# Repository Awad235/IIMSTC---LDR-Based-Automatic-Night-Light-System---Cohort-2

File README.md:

# 🌙 LDR Based Automatic Night Light System

---

## 📋 Overview

The **LDR Based Automatic Night Light System** is a simple, energy-efficient automatic lighting controller. It uses a Light Dependent Resistor (LDR) to detect ambient light levels and automatically turns an LED ON during darkness and OFF during daylight.

This project demonstrates:
- Light sensing using LDR
- Transistor-based switching
- PCB design using KiCad
- Sustainable energy usage (aligns with SDG 7: Affordable and Clean Energy)

**Designed & simulated in KiCad**  
**Power Supply:** 5V DC

---

## ✨ Features

- Fully automatic operation (no manual switch needed)
- Low power consumption
- Cost-effective and easy to build
- Compact PCB design
- Real-world applications: street lights, garden lights, corridor lighting, security systems

---

## 🛠️ Components Used

| Sl. No | Component                  | Specification                  |
|--------|----------------------------|--------------------------------|
| 1      | Light Dependent Resistor   | LDR03 Photoresistor            |
| 2      | Transistor                 | BC817-40 (NPN)                 |
| 3      | LED                        | SML-LX1206SUGC-TR (Green)      |
| 4      | Resistor R1                | 82 kΩ                          |
| 5      | Resistor R2                | 82 kΩ                          |
| 6      | DC Power Connector         | 2-Pin connector (J1)           |
| 7      | Power Supply               | 5V DC                          |

**Note:** The schematic file (source of truth) shows R2 = 82 kΩ.

---

## 📐 Circuit Schematic

**Key Connections:**
- LDR (R3) + R1 form voltage divider for transistor base
- Q1 (BC817-40) acts as electronic switch
- R2 limits current through the LED

---

## 🖨️ PCB Layout

---

## 📦 3D View

)

---

## 🔬 How It Works

The system works on the principle of variation in resistance of the LDR with respect to light intensity.

- **Daytime (bright light):** LDR resistance drops sharply → voltage at transistor base becomes too low → transistor stays OFF → LED remains OFF.
- **Nighttime (low light):** LDR resistance increases significantly → sufficient base voltage turns the transistor ON → current flows through R2 and LED → LED glows automatically.

The transistor (BC817-40) acts as a simple electronic switch, and the whole circuit runs on 5V DC with zero standby power when the LED is off.

---

## 🚀 How to Build & Test

1. Use the provided KiCad schematic & layout (or recreate from images)
2. Fabricate the PCB
3. Solder components exactly as shown in the 3D view
4. Connect 5V DC supply to J1
5. Cover the LDR with your hand → LED should turn ON
6. Shine light on the LDR → LED should turn OFF

**Pro tip:** Test everything on a breadboard first before soldering!

---

## 🛡️ License

Open-source under the **MIT License**. Feel free to use, modify, and share!

---

**Made with ❤️ in Bengaluru**  
**Last updated:** March 2026

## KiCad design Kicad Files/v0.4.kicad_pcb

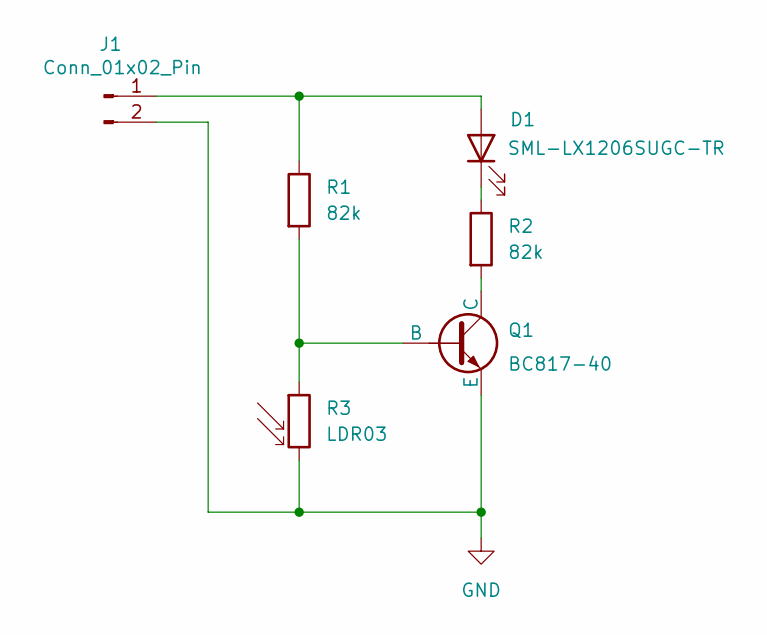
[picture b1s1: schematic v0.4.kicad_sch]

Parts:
D1: SML-LX1206SUGC-TR; LED_1206_3216Metric
J1: Conn_01x02_Pin; PinHeader_1x02_P2.54mm_Vertical
Q1: BC817-40; SOT-23
R1, R2: 82k; R_1206_3216Metric
R3: LDR03; R_LDR_10x8.5mm_P7.6mm_Vertical

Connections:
GND: J1.2, Q1.3 (E), R3.2
unnamed: D1.2 (A), J1.1, R1.1
unnamed: D1.1 (K), R2.1
unnamed: Q1.2 (B), R1.2, R3.1
unnamed: Q1.1 (C), R2.2

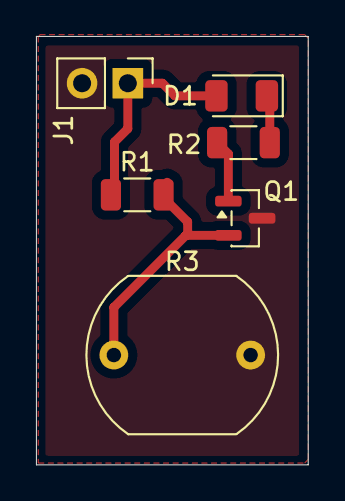
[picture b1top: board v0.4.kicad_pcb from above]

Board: 2 copper layers, 15.1 x 23.8 mm, 6 parts (0 on the bottom side), 5 nets.

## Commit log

2026-03-12 Create kic
2026-03-12 Added KiCad schematic and PCB design files
2026-03-12 Revise README with comprehensive project details
    Expanded the README to include detailed project overview, features, components, circuit schematic, PCB layout, and instructions for building and testing the LDR based automatic night light system.
2026-03-12 Update README to clarify resistor value and report
    Removed mention of the report PDF and updated note for R2.
2026-03-12 Revise README title and cleanup instructions
    Updated project title with emoji and removed maintenance instructions.
2026-03-12 Remove project cover image from README
2026-03-12 Remove internship project note from README
2026-03-12 Update image link for 3D Render in README
2026-03-12 Fix image link syntax in README.md
